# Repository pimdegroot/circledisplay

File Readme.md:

# Circle Display 

## Introduction
This repository contains all the design files, production files and example code for a simple circular LED display.

This readme assumes that you either know how to produce a board, source parts, and solder SMD components, or are willing to learn how to do these things. The production files have been tested using several production methods, so you shouldn't encounter issues making this board. The hints and instructions included should be enough to get you started.

## Parts

The following components are needed:

* 1x 74HC595 shift register in SOP16 package
* 3x 100nF capacitor in a 0805 package
* 8x 1k 0805 resistor
* 16x LED in a 1206 package
* 2x 2N7002 mosfet
* 2x 10k 0805 resistor (R1 and R2)
* 2x 4.5x4.5mm push button
* 1x 6x2 angled header

Notes:
1. The 1k resistors are for controlling the brightness of the LEDs and have been picked to get a reasonable amount of light, without being blinding. Use a lower value resistor for brighter LEDs. 
2. You can use any 1206 LED. If you don't know what color to use, you can get packages with small amounts of multiple colors from aliexpress/ebay.
3. The BOM can be found here: [circledisplay.csv](hardware/gerbers/circledisplay.csv) and contains article numbers for [LCSC.com](http://lcsc.com)

## Boards

Production files can be found in the [hardware/gerbers/](hardware/gerbers/) folder. Most vendors will accept the [zip file](hardware/gerbers/circledisplay.zip) with gerbers. Examples are Oshpark, JLCPCB, PCBWAY, and Dirtypcbs

Two vendors have been tested:

### Oshpark

L to R: After dark, Purple, Flex

[Oshpark](http://oshpark.com) is an American PCB manufacturer that specializes in small run prototype boards. They have decent prices for small orders and excellent customer service. They only do three types of boards: After dark, which is black substrate with clear solder mask. This shows the copper layers while also protecting them with a clear coat. Purple, which is their standard color. And flex, which are flexible pcbs. This design is not made for flex and it is not recommended to pick this option. All boards are made with gold plated solder pads and the default shipping option is free. You get three boards.

If you have never ordered pcb's you can't go wrong with Oshpark

### JLCPCB

All the possible soldermask colors of JLC

[JLCPCB](http://jlcpcb.com) is a Chinese PCB manufacturer. They have a prototype service, but can also do large quantities of boards. They offer much more options, like soldermask colors and plating material. With the default options they are similar in price as Oshpark for 5 boards, but if you order larger quantities the price per board drops significantly. Another advantage is that you can order solderpaste stencils with your pcbs.

Note that JLCPCB adds an order number to your PCBs. Click "specify location" at the remove ordernumber option to put that number under the chip. The required JLCJLCJLCJLC silkscreen is already under the chip.

SMT assembled boards

JLCPCB also offers a SMT assembly service, where you can get fully assembled boards. In addition to the zip file, you also need the [BOM](hardware/gerbers/circledisplay.csv) and the [placement file](hardware/gerbers/circledisplay-top-pos.csv). Note that these files have been manually corrected for parts rotation, so take extra care when re-exporting them from the kicad files. The headers aren't included in the files, as they add quite a bit of assembly costs.

If you just want the finished product this is the way to go. If you want to make your own boards in the future, I would recommend to start with getting the parts and boards and soldering them yourself. Getting boards ready for SMT adds another layer of complexity and isn't recommended for a beginner.

## Soldering

This readme doesn't have a soldering guide (yet). This board is similar enough to an older board that this guide: [https://github.com/pimdegroot/74595displaykit](https://github.com/pimdegroot/74595displaykit) translates to this board as well.

## Software

Software examples can be found in the [software/](software/) folder. Both Arduino and Circuitpython examples are offered. Note that you have to change the pinout to your dev board.

The circle is divided in groups of 8 LEDs. Mosfet A controls the right group and mosfet B the left one. The pins have the following functions:
* SER is the serial data in pin. Data should be shifted in most significant bit first.
* CLK shifts in the bit at the SER pin when going high
* LAT latches the data, shifting it from a temporary register to the output
* OE is output enable, and makes the chip output when low.
* MA and MB are the mosfets
* BTN1 is the top button, BTN2 is the lower button

The procedure for driving the 74HC595 is as follows:

### Setup
Drive SER, CLK, LAT, OE, MA and MB low. Set BTN1 and BTN2 as input.

### Update loop

Right side:
* Shift in the bits for the right side of the display, MSB first
* Set MB low
* Set LAT high
* Set MA high
* Set LAT low

Left side:
* Shift in the bits for the left side of the display, MSB first
* Set MA low
* Set LAT high
* Set MB high
* Set LAT low

## Final notes

The information in this repository is provided as is, and while care has been taken to eliminate all errors, there might still be bugs. As I have limited time to give support, please try to solve the problem yourself first. If you found an error in the repo, I would like to hear it in the form of an issue so I can fix it for everyone.

Have fun building the board, and I would love to see the results. You can contact me at [https://twitter.com/mifune](https://twitter.com/mifune)

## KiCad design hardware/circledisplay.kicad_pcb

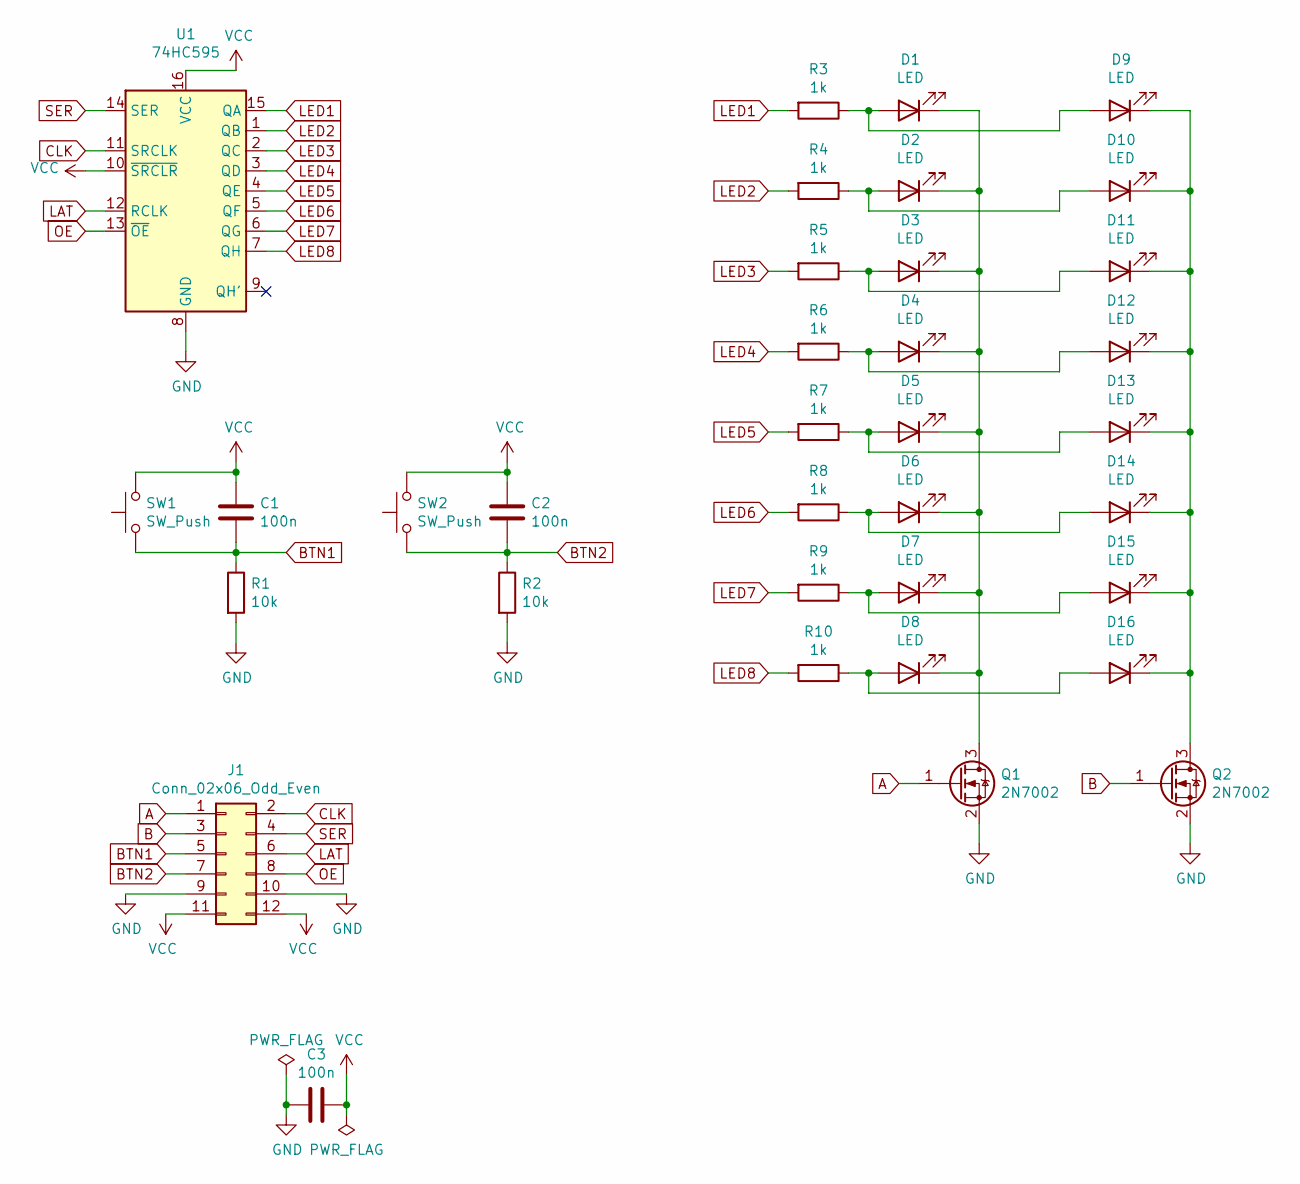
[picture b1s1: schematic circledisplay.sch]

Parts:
C1, C2, C3: 100n; C_0805_2012Metric; LCSC C49678
D1, D2, D3, D4, D5, D6, D7, D8, D9, D10, D11, D12, D13, D14, D15, D16: LED; LED_1206_3216Metric; LCSC C93094
J1: Conn_02x06_Odd_Even; PinHeader_2x06_P2.54mm_Vertical
Q1, Q2: 2N7002; SOT-23; LCSC C8545
R1, R2: 10k; R_0805_2012Metric; LCSC C17414
R3, R4, R5, R6, R7, R8, R9, R10: 1k; R_0805_2012Metric; LCSC C17513
SW1, SW2: SW_Push; SW; LCSC C174049
U1: 74HC595; SOIC-16_3.9x9.9mm_P1.27mm; LCSC C5947

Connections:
A: J1.1, Q1.1 (G)
B: J1.3, Q2.1 (G)
BTN1: C1.2, J1.5, R1.1, SW1.1
BTN2: C2.2, J1.7, R2.1, SW2.1
CLK: J1.2, U1.11 (SRCLK)
GND: C3.2, J1.9, J1.10, Q1.2 (S), Q2.2 (S), R1.2, R2.2, U1.8 (GND)
LAT: J1.6, U1.12 (RCLK)
LED1: R3.2, U1.15 (QA)
LED2: R4.2, U1.1 (QB)
LED3: R5.2, U1.2 (QC)
LED4: R6.2, U1.3 (QD)
LED5: R7.2, U1.4 (QE)
LED6: R8.2, U1.5 (QF)
LED7: R9.2, U1.6 (QG)
LED8: R10.2, U1.7 (QH)
unnamed: D1.1 (K), D2.1 (K), D3.1 (K), D4.1 (K), D5.1 (K), D6.1 (K), D7.1 (K), D8.1 (K), Q1.3 (D)
unnamed: D1.2 (A), D9.2 (A), R3.1
unnamed: D9.1 (K), D10.1 (K), D11.1 (K), D12.1 (K), D13.1 (K), D14.1 (K), D15.1 (K), D16.1 (K), Q2.3 (D)
unnamed: D2.2 (A), D10.2 (A), R4.1
unnamed: D3.2 (A), D11.2 (A), R5.1
unnamed: D4.2 (A), D12.2 (A), R6.1
unnamed: D5.2 (A), D13.2 (A), R7.1
unnamed: D6.2 (A), D14.2 (A), R8.1
unnamed: D7.2 (A), D15.2 (A), R9.1
unnamed: D8.2 (A), D16.2 (A), R10.1
OE: J1.8, U1.13 (~OE)
SER: J1.4, U1.14 (SER)
VCC: C1.1, C2.1, C3.1, J1.11, J1.12, SW1.2, SW2.2, U1.10 (~SRCLR), U1.16 (VCC)

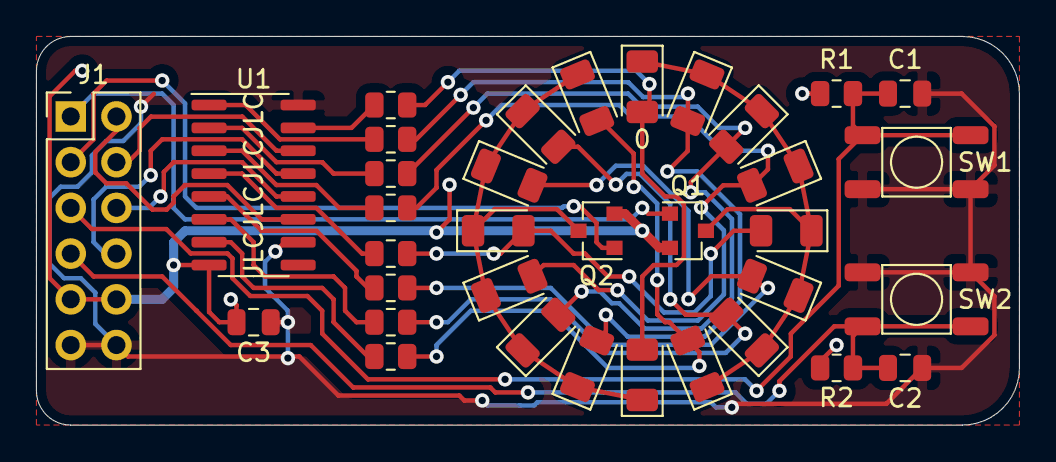
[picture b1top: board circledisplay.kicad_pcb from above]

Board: 2 copper layers, 54.6 x 21.6 mm, 35 parts (0 on the bottom side), 28 nets.

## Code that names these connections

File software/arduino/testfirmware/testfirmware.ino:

#define CLK 2
#define SDI 3
#define LE  4
#define OE  5

#define MA  6
#define MB  7
#define BTN1 8
#define BTN2 9

#define LED1 22
#define LED2 23

void setup() {
  pinMode(CLK, OUTPUT);
  pinMode(SDI, OUTPUT);
  pinMode(LE, OUTPUT);
  pinMode(OE, OUTPUT);

  pinMode(MA, OUTPUT);
  pinMode(MB, OUTPUT);
  pinMode(BTN1, INPUT);
  pinMode(BTN2, INPUT);

  pinMode(LED1, OUTPUT);
  pinMode(LED2, OUTPUT);

  digitalWrite(CLK, LOW);
  digitalWrite(SDI, LOW);
  digitalWrite(LE, LOW);
  digitalWrite(OE, LOW);

  digitalWrite(MA, LOW);
  digitalWrite(MB, LOW);

  digitalWrite(LED1, LOW);
  digitalWrite(LED2, LOW);

  shiftOut(SDI,CLK,LSBFIRST,255);

  digitalWrite(LE,HIGH);
  digitalWrite(LE,LOW);
  

}

void loop() {
  // put your main code here, to run repeatedly:
  digitalWrite(MA,HIGH);
  delay(2);
  digitalWrite(MA,LOW);
  //delay(1);

  digitalWrite(MB,HIGH);
  delay(2);
  digitalWrite(MB,LOW);
  //delay(1);

  digitalWrite(LED1,digitalRead(BTN1));
  digitalWrite(LED2,digitalRead(BTN2));

}

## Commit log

2021-05-02 Initial commit
    Created the repository for the circle display
2021-05-02 Add kitspace.yaml
2021-05-02 Add quantity column to BOM
2021-05-02 Add EDA info to kitspace.yaml
